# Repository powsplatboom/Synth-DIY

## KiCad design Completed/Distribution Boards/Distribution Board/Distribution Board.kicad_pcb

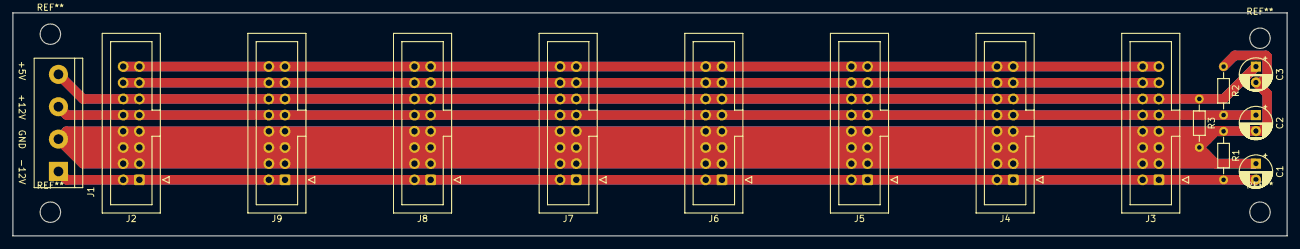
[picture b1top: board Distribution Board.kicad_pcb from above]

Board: 2 copper layers, 200.0 x 35.0 mm, 15 parts (0 on the bottom side), 6 nets.

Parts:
C1, C2, C3: 47uf; CP_Radial_D5.0mm_P2.50mm
J1: Conn_01x04_Female; TerminalBlock_bornier-4_P5.08mm
J2, J3, J4, J5, J6, J7, J8, J9: Conn_02x08_Odd_Even; IDC-Header_2x08_P2.54mm_Vertical
R1, R2, R3: 10k; R_Axial_DIN0204_L3.6mm_D1.6mm_P7.62mm_Horizontal

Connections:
unnamed: C1.1, C2.2, C3.2, J1.2, J2.3, J2.4, J2.5, J2.6, J2.7, J2.8, J3.3, J3.4, J3.5, J3.6, J3.7, J3.8, J4.3, J4.4, J4.5, J4.6, J4.7, J4.8, J5.3, J5.4, J5.5, J5.6, J5.7, J5.8, J6.3, J6.4, J6.5, J6.6, J6.7, J6.8, J7.3, J7.4, J7.5, J7.6, J7.7, J7.8, J8.3, J8.4, J8.5, J8.6, J8.7, J8.8, J9.3, J9.4, J9.5, J9.6, J9.7, J9.8, R1.1, R2.2, R3.2
unnamed: C1.2, J1.1, J2.1, J2.2, J3.1, J3.2, J4.1, J4.2, J5.1, J5.2, J6.1, J6.2, J7.1, J7.2, J8.1, J8.2, J9.1, J9.2, R1.2
unnamed: C2.1, J1.3, J2.9, J2.10, J3.9, J3.10, J4.9, J4.10, J5.9, J5.10, J6.9, J6.10, J7.9, J7.10, J8.9, J8.10, J9.9, J9.10, R2.1
unnamed: C3.1, J1.4, J2.11, J2.12, J3.11, J3.12, J4.11, J4.12, J5.11, J5.12, J6.11, J6.12, J7.11, J7.12, J8.11, J8.12, J9.11, J9.12, R3.1
unnamed: J2.13, J2.14, J3.13, J3.14, J4.13, J4.14, J5.13, J5.14, J6.13, J6.14, J7.13, J7.14, J8.13, J8.14, J9.13, J9.14
unnamed: J2.15, J2.16, J3.15, J3.16, J4.15, J4.16, J5.15, J5.16, J6.15, J6.16, J7.15, J7.16, J8.15, J8.16, J9.15, J9.16

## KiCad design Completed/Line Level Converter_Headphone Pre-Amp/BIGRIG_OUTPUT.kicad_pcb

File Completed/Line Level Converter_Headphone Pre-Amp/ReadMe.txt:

Eurorack to line level output converter that I use in my DIY modular.

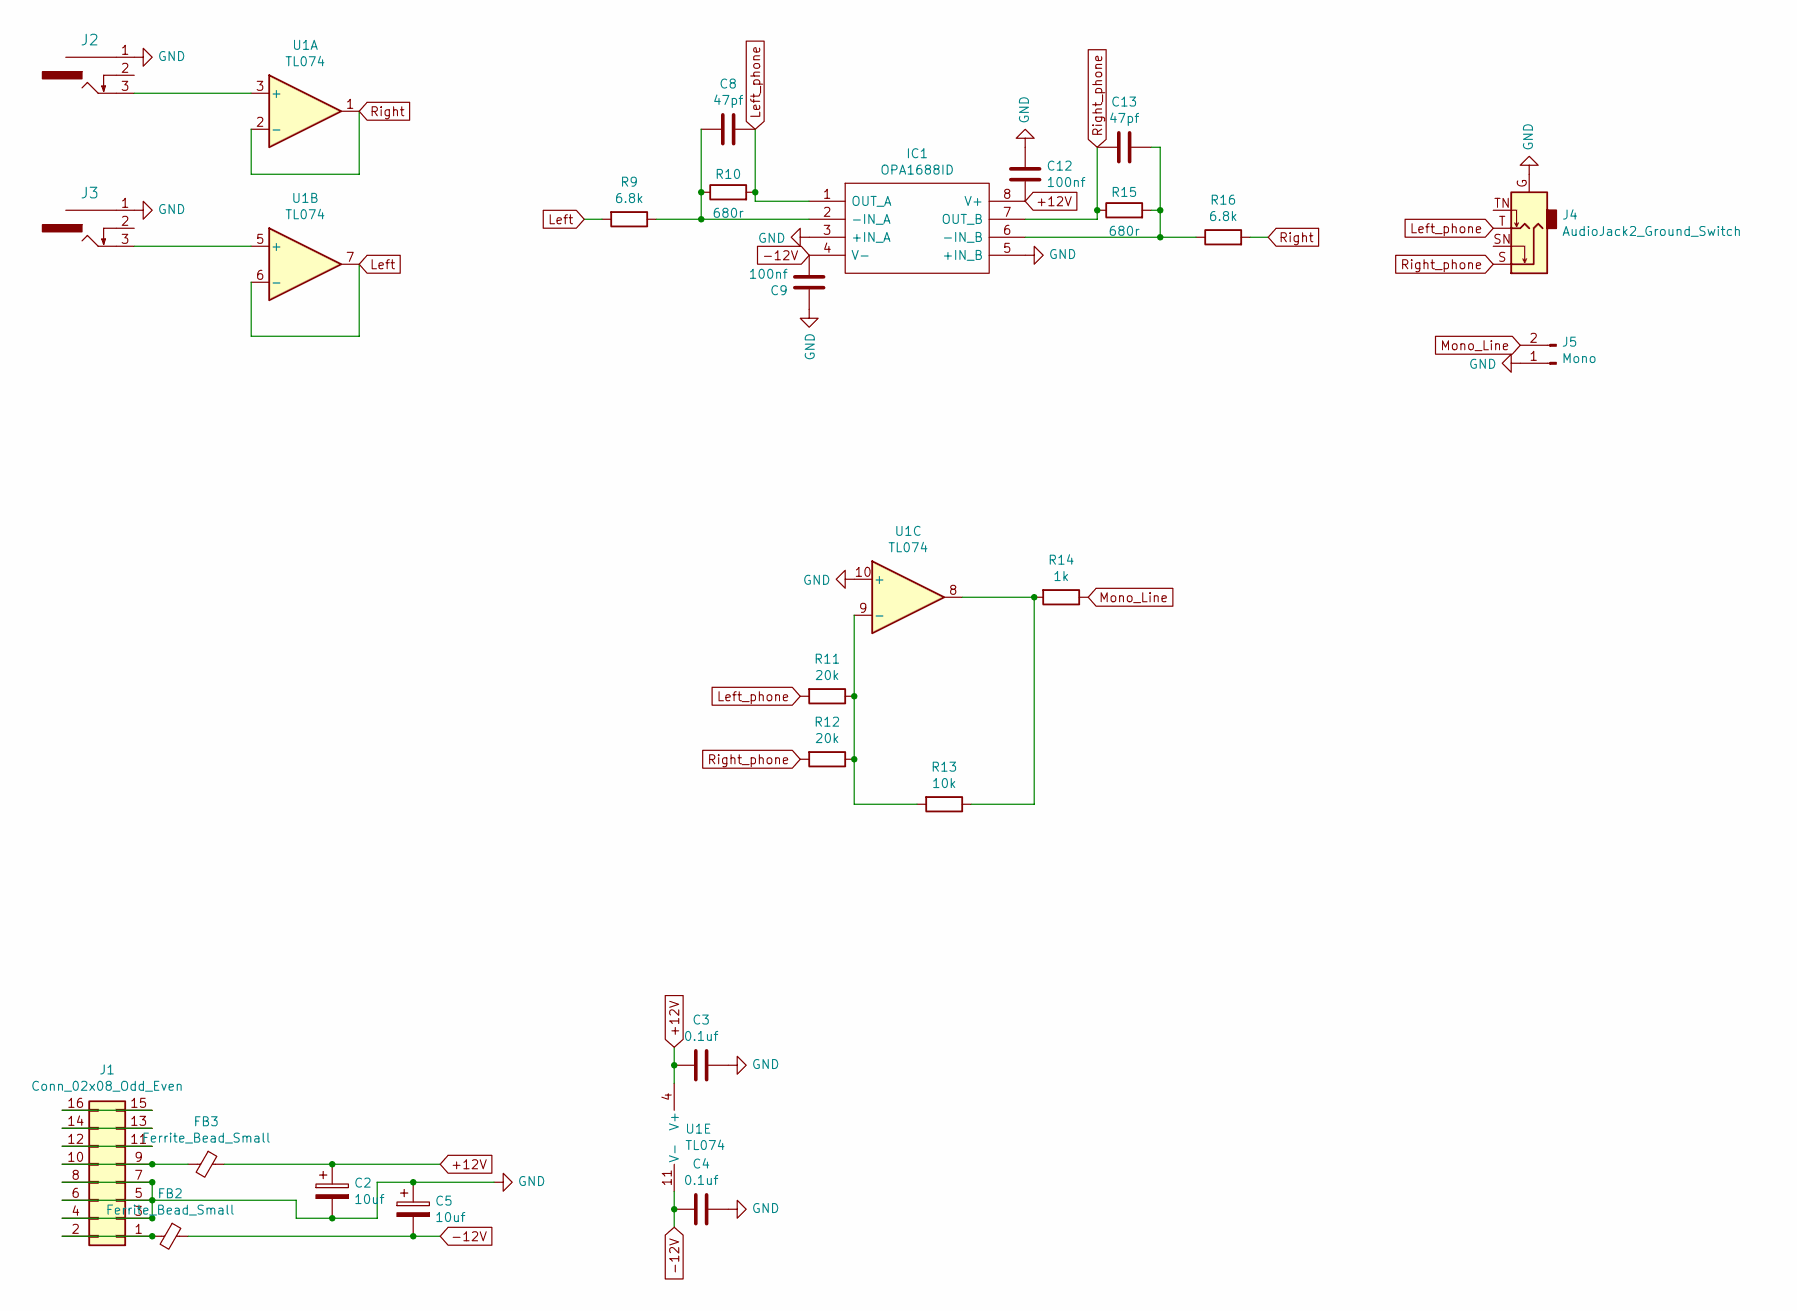
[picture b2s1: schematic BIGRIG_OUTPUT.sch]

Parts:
C2, C5: 10uf; CP_Radial_D5.0mm_P2.50mm
C3, C4: 0.1uf; C_Disc_D4.7mm_W2.5mm_P5.00mm
C8, C13: 47pf; C_Disc_D4.7mm_W2.5mm_P5.00mm
C9, C12: 100nf; C_Disc_D4.7mm_W2.5mm_P5.00mm
FB2, FB3: Ferrite_Bead_Small; L_Axial_L5.0mm_D3.6mm_P10.00mm_Horizontal_Murata_BL01RN1A2A2
IC1: OPA1688ID; SOIC-8_3.9x4.9mm_P1.27mm; Manufacturer_Part_Number OPA1688ID; Mouser Part Number 595-OPA1688ID
J1: Conn_02x08_Odd_Even; IDC-Header_2x08_P2.54mm_Vertical
J2: Right; PJ-3001_Mono_Phone
J3: Left; PJ-3001_Mono_Phone
J4: AudioJack2_Ground_Switch; Stereo_phon_jack_STX-3790
J5: Mono; JST_EH_B2B-EH-A_1x02_P2.50mm_Vertical
R9, R16: 6.8k; R_Axial_DIN0204_L3.6mm_D1.6mm_P7.62mm_Horizontal
R10, R15: 680r; R_Axial_DIN0204_L3.6mm_D1.6mm_P7.62mm_Horizontal
R11, R12: 20k; R_Axial_DIN0204_L3.6mm_D1.6mm_P7.62mm_Horizontal
R13: 10k; R_Axial_DIN0204_L3.6mm_D1.6mm_P7.62mm_Horizontal
R14: 1k; R_Axial_DIN0204_L3.6mm_D1.6mm_P7.62mm_Horizontal
U1: TL074; DIP-14_W7.62mm_LongPads

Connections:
+12V: C2.1, C3.2, C12.2, FB3.1, IC1.8 (V+), U1.4 (V+)
-12V: C4.2, C5.2, C9.2, FB2.1, IC1.4 (V-), U1.11 (V-)
GND: C2.2, C3.1, C4.1, C5.1, C9.1, C12.1, IC1.3 (+IN_A), IC1.5 (+IN_B), J1.3, J1.4, J1.5, J1.6, J1.7, J1.8, J2.1, J3.1, J4.G, J5.1, U1.10 (+)
Left: R9.2, U1.6 (-), U1.7
Left_phone: C8.1, IC1.1 (OUT_A), J4.T, R10.2, R11.2
Mono_Line: J5.2, R14.1
unnamed: C8.2, IC1.2 (-IN_A), R9.1, R10.1
unnamed: C13.1, IC1.6 (-IN_B), R15.2, R16.1
unnamed: FB2.2, J1.1, J1.2
unnamed: FB3.2, J1.9, J1.10
unnamed: J1.11, J1.12
unnamed: J1.13, J1.14
unnamed: J1.15, J1.16
unnamed: J2.3, U1.3 (+)
unnamed: J3.3, U1.5 (+)
unnamed: R11.1, R12.1, R13.2, U1.9 (-)
unnamed: R13.1, R14.2, U1.8
Right: R16.2, U1.1, U1.2 (-)
Right_phone: C13.2, IC1.7 (OUT_B), J4.S, R12.2, R15.1

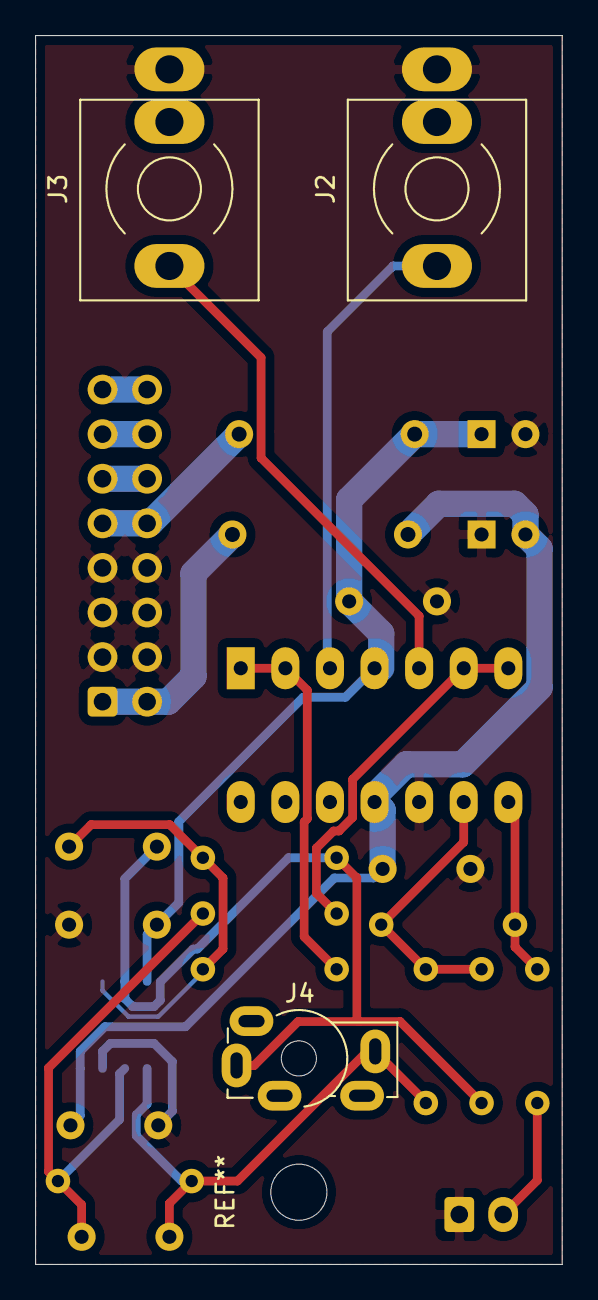
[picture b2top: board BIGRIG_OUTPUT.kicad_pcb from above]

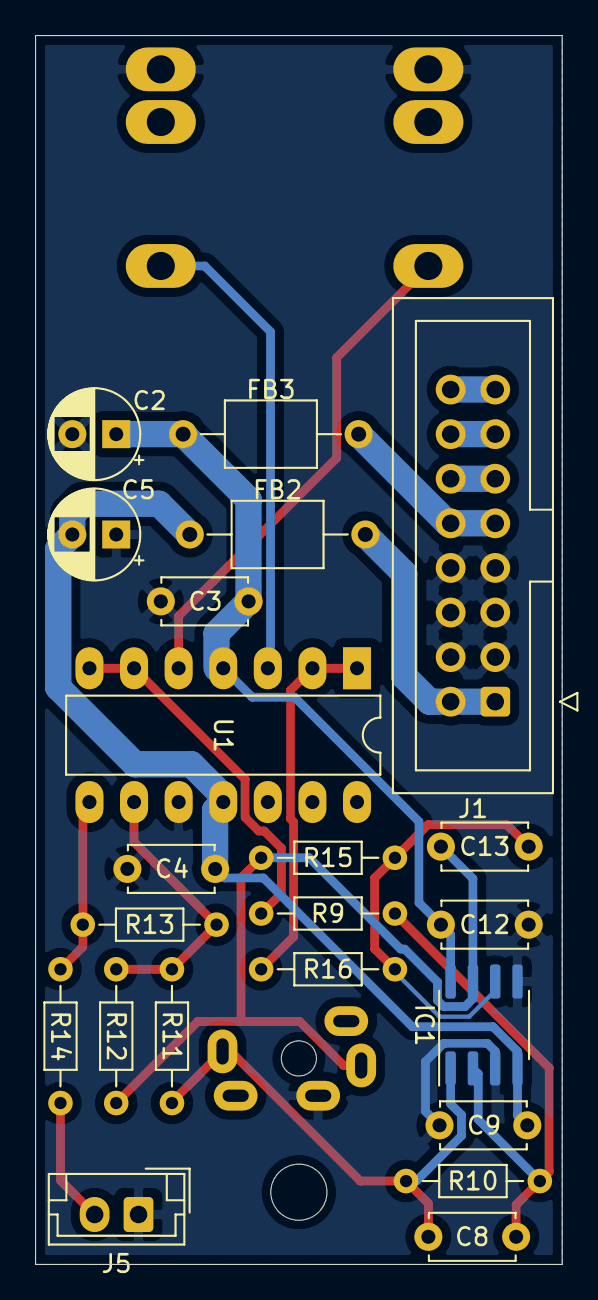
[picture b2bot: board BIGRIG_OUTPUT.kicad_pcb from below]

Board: 2 copper layers, 30.0 x 70.0 mm, 25 parts (22 on the bottom side), 19 nets.

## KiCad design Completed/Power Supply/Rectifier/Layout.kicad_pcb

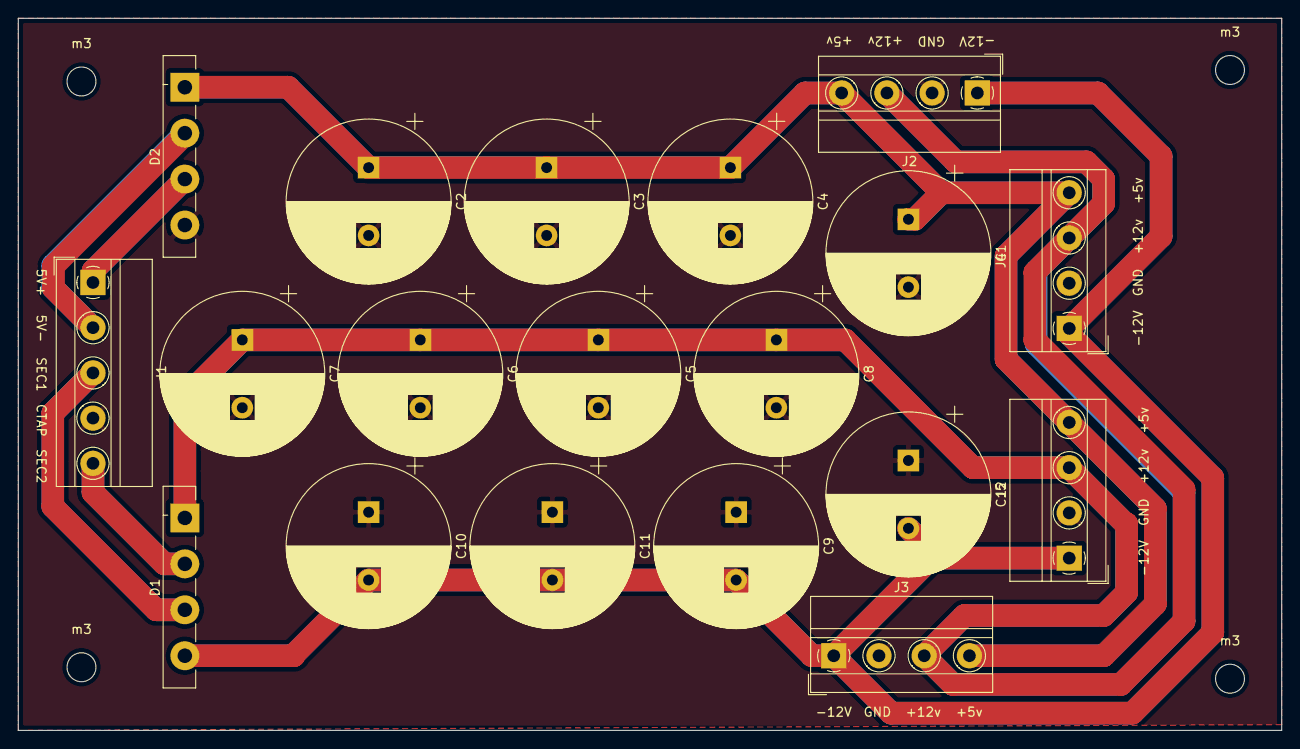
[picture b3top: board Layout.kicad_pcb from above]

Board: 2 copper layers, 139.7 x 78.7 mm, 23 parts (0 on the bottom side), 8 nets.

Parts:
C1, C2, C3, C4, C5, C6, C7, C8, C9, C10, C11, C12: 10000uf; CP_Radial_D18.0mm_P7.50mm
D1, D2: GBU8A; Diode_Bridge_Vishay_GBU
J1: Transformer Outputs; TerminalBlock_MetzConnect_Type011_RT05505HBWC_1x05_P5.00mm_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
J2, J3, J4, J5: Conn_01x04_Male; TerminalBlock_MetzConnect_Type011_RT05504HBWC_1x04_P5.00mm_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
m3, m3#2, m3#3, m3#4: MountingHole_3.2mm_M3

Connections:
GND: C1.2, C2.2, C3.2, C4.2, C5.2, C6.2, C7.2, C8.2, C9.1, C10.1, C11.1, C12.1, D2.4, J1.4, J2.2, J3.2, J4.2, J5.2
unnamed: C1.1, C2.1, C3.1, C4.1, D2.1, J2.4, J3.4, J4.4, J5.4
unnamed: C5.1, C6.1, C7.1, C8.1, D1.1, J2.3, J3.3, J4.3, J5.3
unnamed: C9.2, C10.2, C11.2, C12.2, D1.4, J2.1, J3.1, J4.1, J5.1
unnamed: D1.2, J1.5
unnamed: D1.3, J1.3
unnamed: D2.2, J1.2
unnamed: D2.3, J1.1
